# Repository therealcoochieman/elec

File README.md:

# KikiMorse - schematics

Kicad schematics for a simple stm32-base keyboard to morse device

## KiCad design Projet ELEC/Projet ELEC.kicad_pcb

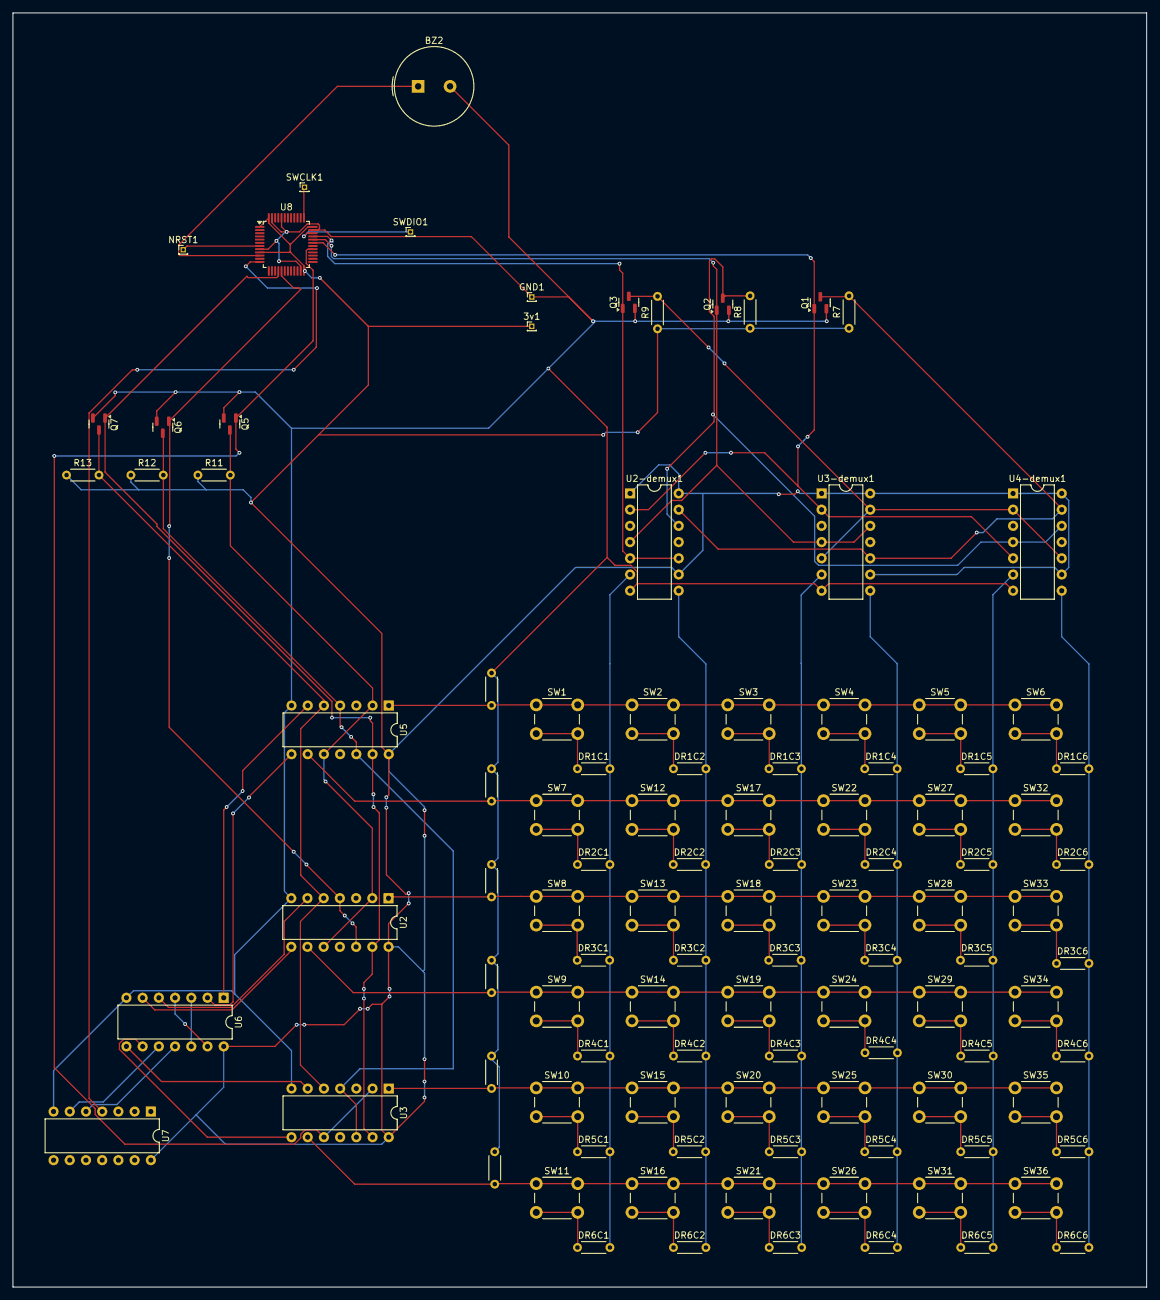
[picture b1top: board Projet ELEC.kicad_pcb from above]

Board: 2 copper layers, 177.6 x 199.6 mm, 105 parts (0 on the bottom side), 77 nets.

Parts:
3v1: Conn_01x01_MountingPin; PinHeader_1x01_P1.00mm_Vertical
BZ2: Buzzer; Buzzer_TDK_PS1240P02BT_D12.2mm_H6.5mm
DR1C1, DR1C2, DR1C3, DR1C4, DR1C5, DR1C6, DR2C1, DR2C2, DR2C3, DR2C4, DR2C5, DR2C6, DR3C1, DR3C2, DR3C3, DR3C4, DR3C5, DR3C6, DR4C1, DR4C2, DR4C3, DR4C4, DR4C5, DR4C6, DR5C1, DR5C2, DR5C3, DR5C4, DR5C5, DR5C6, DR6C1, DR6C2, DR6C3, DR6C4, DR6C5, DR6C6: D; R_Axial_DIN0204_L3.6mm_D1.6mm_P5.08mm_Horizontal
GND1: Conn_01x01_MountingPin; PinHeader_1x01_P1.00mm_Vertical
NRST1: Conn_01x01_MountingPin; PinHeader_1x01_P1.00mm_Vertical
Q1, Q2, Q3, Q5, Q6, Q7: ZXM61N02F; SOT-23
R1, R2, R3, R4, R5, R6, R7, R8, R9, R11, R12, R13: 1000; R_Axial_DIN0204_L3.6mm_D1.6mm_P5.08mm_Horizontal
SW1: SWR1C1; SW_PUSH_6mm
SW2: SWR1C2; SW_PUSH_6mm
SW3: SWR1C3; SW_PUSH_6mm
SW4: SWR1C4; SW_PUSH_6mm
SW5: SWR1C5; SW_PUSH_6mm
SW6: SWR1C6; SW_PUSH_6mm
SW7: SWR2C1; SW_PUSH_6mm
SW8: SWR3C1; SW_PUSH_6mm
SW9: SWR4C1; SW_PUSH_6mm
SW10: SWR5C1; SW_PUSH_6mm
SW11: SWR6C1; SW_PUSH_6mm
SW12: SWR2C2; SW_PUSH_6mm
SW13: SWR3C2; SW_PUSH_6mm
SW14: SWR4C2; SW_PUSH_6mm
SW15: SWR5C2; SW_PUSH_6mm
SW16: SWR6C2; SW_PUSH_6mm
SW17: SWR2C3; SW_PUSH_6mm
SW18: SWR3C3; SW_PUSH_6mm
SW19: SWR4C3; SW_PUSH_6mm
SW20: SWR5C3; SW_PUSH_6mm
SW21: SWR6C3; SW_PUSH_6mm
SW22: SWR2C4; SW_PUSH_6mm
SW23: SWR3C4; SW_PUSH_6mm
SW24: SWR4C4; SW_PUSH_6mm
SW25: SWR5C4; SW_PUSH_6mm
SW26: SWR6C4; SW_PUSH_6mm
SW27: SWR2C5; SW_PUSH_6mm
SW28: SWR3C5; SW_PUSH_6mm
SW29: SWR4C5; SW_PUSH_6mm
SW30: SWR5C5; SW_PUSH_6mm
SW31: SWR6C5; SW_PUSH_6mm
SW32: SWR2C6; SW_PUSH_6mm
SW33: SWR3C6; SW_PUSH_6mm
SW34: SWR4C6; SW_PUSH_6mm
SW35: SWR5C6; SW_PUSH_6mm
SW36: SWR6C6; SW_PUSH_6mm
SWCLK1: Conn_01x01_MountingPin; PinHeader_1x01_P1.00mm_Vertical
SWDIO1: Conn_01x01_MountingPin; PinHeader_1x01_P1.00mm_Vertical
U2, U2-demux1, U3, U3-demux1, U4-demux1, U5: 74LS21; DIP-14_W7.62mm
U6, U7: 4071; DIP-14_W7.62mm
U8: STM32F103C8Tx; LQFP-48_7x7mm_P0.5mm

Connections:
+3.3V: 3v1.1, R7.1, R8.1, R9.1, R11.1, R12.1, R13.1, U2.14 (VCC), U2-demux1.1, U2-demux1.9, U2-demux1.14 (VCC), U3.14 (VCC), U3-demux1.1, U3-demux1.9, U3-demux1.14 (VCC), U4-demux1.1, U4-demux1.9, U4-demux1.14 (VCC), U5.14 (VCC), U6.14 (VDD), U7.14 (VDD), U8.1 (VBAT), U8.9 (VDDA), U8.24 (VDD), U8.36 (VDD), U8.48 (VDD)
A0: Q7.1 (G), U2.13, U3.13, U5.13, U8.16 (PA6)
A1: Q6.1 (G), U2.4, U2.12, U8.17 (PA7)
A2: Q5.1 (G), U3.2, U3.10, U8.29 (PA8)
Col1: DR1C1.2 (A), DR2C1.2 (A), DR3C1.2 (A), DR4C1.2 (A), DR5C1.2 (A), DR6C1.2 (A), U2-demux1.6
Col2: DR1C2.2 (A), DR2C2.2 (A), DR3C2.2 (A), DR4C2.2 (A), DR5C2.2 (A), DR6C2.2 (A), U2-demux1.8
Col3: DR1C3.2 (A), DR2C3.2 (A), DR3C3.2 (A), DR4C3.2 (A), DR5C3.2 (A), DR6C3.2 (A), U3-demux1.6
Col4: DR1C4.2 (A), DR2C4.2 (A), DR3C4.2 (A), DR4C4.2 (A), DR5C4.2 (A), DR6C4.2 (A), U3-demux1.8
Col5: DR1C5.2 (A), DR2C5.2 (A), DR3C5.2 (A), DR4C5.2 (A), DR5C5.2 (A), DR6C5.2 (A), U4-demux1.6
Col6: DR1C6.2 (A), DR2C6.2 (A), DR3C6.2 (A), DR4C6.2 (A), DR5C6.2 (A), DR6C6.2 (A), U4-demux1.8
GND: BZ2.2 (-), GND1.1, Q1.2 (S), Q2.2 (S), Q3.2 (S), Q5.2 (S), Q6.2 (S), Q7.2 (S), R1.2, R2.2, R3.2, R4.2, R5.2, R6.2, U2.7 (GND), U2-demux1.7 (GND), U3.7 (GND), U3-demux1.7 (GND), U4-demux1.7 (GND), U5.7 (GND), U6.7 (VSS), U7.7 (VSS), U8.8 (VSSA), U8.23 (VSS), U8.35 (VSS), U8.44 (BOOT0), U8.47 (VSS)
MUX_OUTPUT: U7.4, U8.12 (PA2)
NOT1_IN: Q1.1 (G), U2-demux1.2, U3-demux1.2, U4-demux1.5, U8.31 (PA10)
NOT1_OUT: Q1.3 (D), R7.2, U2-demux1.13, U3-demux1.10, U4-demux1.13
NOT2_IN: Q2.1 (G), U2-demux1.4, U3-demux1.4, U3-demux1.12, U8.32 (PA11)
NOT2_OUT: Q2.3 (D), R8.2, U2-demux1.12, U4-demux1.4, U4-demux1.12
NOT3_IN: Q3.1 (G), U2-demux1.5, U2-demux1.10, U8.33 (PA12)
NOT3_OUT: Q3.3 (D), R9.2, U3-demux1.5, U3-demux1.13, U4-demux1.2, U4-demux1.10
unnamed: BZ2.1 (+), U8.10 (PA0)
unnamed: DR1C1.1 (K), SW1.2
unnamed: DR1C2.1 (K), SW2.2
unnamed: DR1C3.1 (K), SW3.2
unnamed: DR1C4.1 (K), SW4.2
unnamed: DR1C5.1 (K), SW5.2
unnamed: DR1C6.1 (K), SW6.2
unnamed: DR2C1.1 (K), SW7.2
unnamed: DR2C2.1 (K), SW12.2
unnamed: DR2C3.1 (K), SW17.2
unnamed: DR2C4.1 (K), SW22.2
unnamed: DR2C5.1 (K), SW27.2
unnamed: DR2C6.1 (K), SW32.2
unnamed: DR3C1.1 (K), SW8.2
unnamed: DR3C2.1 (K), SW13.2
unnamed: DR3C3.1 (K), SW18.2
unnamed: DR3C4.1 (K), SW23.2
unnamed: DR3C5.1 (K), SW28.2
unnamed: DR3C6.1 (K), SW33.2
unnamed: DR4C1.1 (K), SW9.2
unnamed: DR4C2.1 (K), SW14.2
unnamed: DR4C3.1 (K), SW19.2
unnamed: DR4C4.1 (K), SW24.2
unnamed: DR4C5.1 (K), SW29.2
unnamed: DR4C6.1 (K), SW34.2
unnamed: DR5C1.1 (K), SW10.2
unnamed: DR5C2.1 (K), SW15.2
unnamed: DR5C3.1 (K), SW20.2
unnamed: DR5C4.1 (K), SW25.2
unnamed: DR5C5.1 (K), SW30.2
unnamed: DR5C6.1 (K), SW35.2
unnamed: DR6C1.1 (K), SW11.2
unnamed: DR6C2.1 (K), SW16.2
unnamed: DR6C3.1 (K), SW21.2
unnamed: DR6C4.1 (K), SW26.2
unnamed: DR6C5.1 (K), SW31.2
unnamed: DR6C6.1 (K), SW36.2
unnamed: NRST1.1, U8.7 (NRST)
unnamed: Q5.3 (D), R11.2, U2.2, U2.10, U5.2, U5.10
unnamed: Q6.3 (D), R12.2, U3.4, U3.12, U5.4, U5.12
unnamed: Q7.3 (D), R13.2, U2.5, U3.5, U5.5
unnamed: SWCLK1.1, U8.37 (PA14)
unnamed: SWDIO1.1, U8.34 (PA13)
unnamed: U2.6, U6.5
unnamed: U2.8, U6.6
unnamed: U3.6, U6.8
unnamed: U3.8, U6.9
unnamed: U5.6, U6.1
unnamed: U5.8, U6.2
unnamed: U6.10, U7.6
unnamed: U6.11, U7.5
unnamed: U6.3, U6.12
unnamed: U6.4, U6.13
Row1: R1.1, SW1.1, SW2.1, SW3.1, SW4.1, SW5.1, SW6.1, U5.1
Row2: R2.1, SW7.1, SW12.1, SW17.1, SW22.1, SW27.1, SW32.1, U5.9
Row3: R3.1, SW8.1, SW13.1, SW18.1, SW23.1, SW28.1, SW33.1, U2.1
Row4: R4.1, SW9.1, SW14.1, SW19.1, SW24.1, SW29.1, SW34.1, U2.9
Row5: R5.1, SW10.1, SW15.1, SW20.1, SW25.1, SW30.1, SW35.1, U3.1
Row6: R6.1, SW11.1, SW16.1, SW21.1, SW26.1, SW31.1, SW36.1, U3.9

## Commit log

2024-04-27 add: keyboard schematics
2024-04-27 add: demux 1x6 schematics
2024-04-28 [+] all components gathered in one project
2024-04-28 corrected around 60 errors, removed a 74ls04, and many other improvements
2024-05-10 [~] not gates -> mosfet N
2024-05-10 fix(mux): rename mux output
    * Projet ELEC/mux 6x1.kicad_sch
2024-05-10 feat(stm32): schematics for f103
    * Projet ELEC/stm32.kicad_sch
2024-05-10 feat(st-link): add nucleo 64-l476rg + connect to f103 through swd
    * Projet ELEC/stm32.kicad_sch
2024-05-10 on va mourir mdr
2024-05-10 fix ta merde quentin
2024-05-10 [*] fixed missing gnd for mosfet
2024-05-11 pcb updated
2024-05-11 6x1 almost done, just need to connect VCC/GND
2024-05-11 6x1 PCB done, saved this time
2024-05-11 PCB done, except ST, pin headers and a few resistors not connected to ground
2024-05-11 fixed some switches not connected
2024-05-11 [*] stm32 schematics
2024-05-11 [*] stm32 decoupling caps
2024-05-12 chore: delete keyboard directory
    - Keyboard/Keyboard.kicad_pcb
    - Keyboard/Keyboard.kicad_pro
    - Keyboard/Keyboard.kicad_sch
    - Keyboard/demux 1x6.kicad_sch
2024-05-12 chore: update project to latest version (what's the point of git)
    * Projet ELEC/Projet ELEC.kicad_pcb
    * Projet ELEC/Projet ELEC.kicad_sch
    * Projet ELEC/demux 1x6.kicad_sch
    * Projet ELEC/keyboard.kicad_sch
    * Projet ELEC/mux 6x1.kicad_sch
    * Projet ELEC/stm32.kicad_sch
